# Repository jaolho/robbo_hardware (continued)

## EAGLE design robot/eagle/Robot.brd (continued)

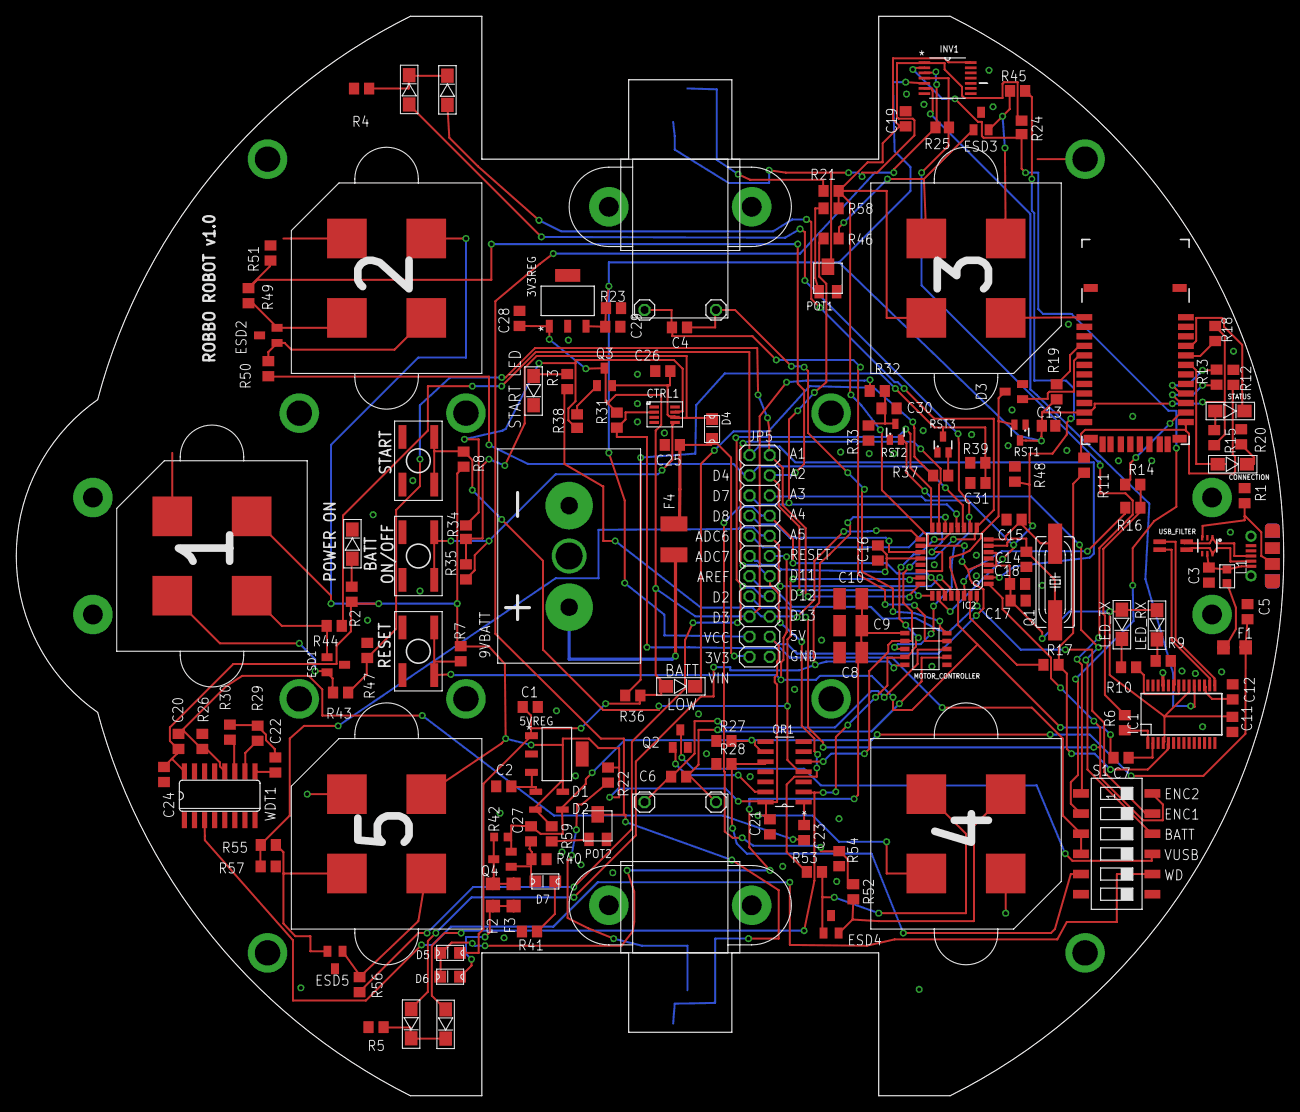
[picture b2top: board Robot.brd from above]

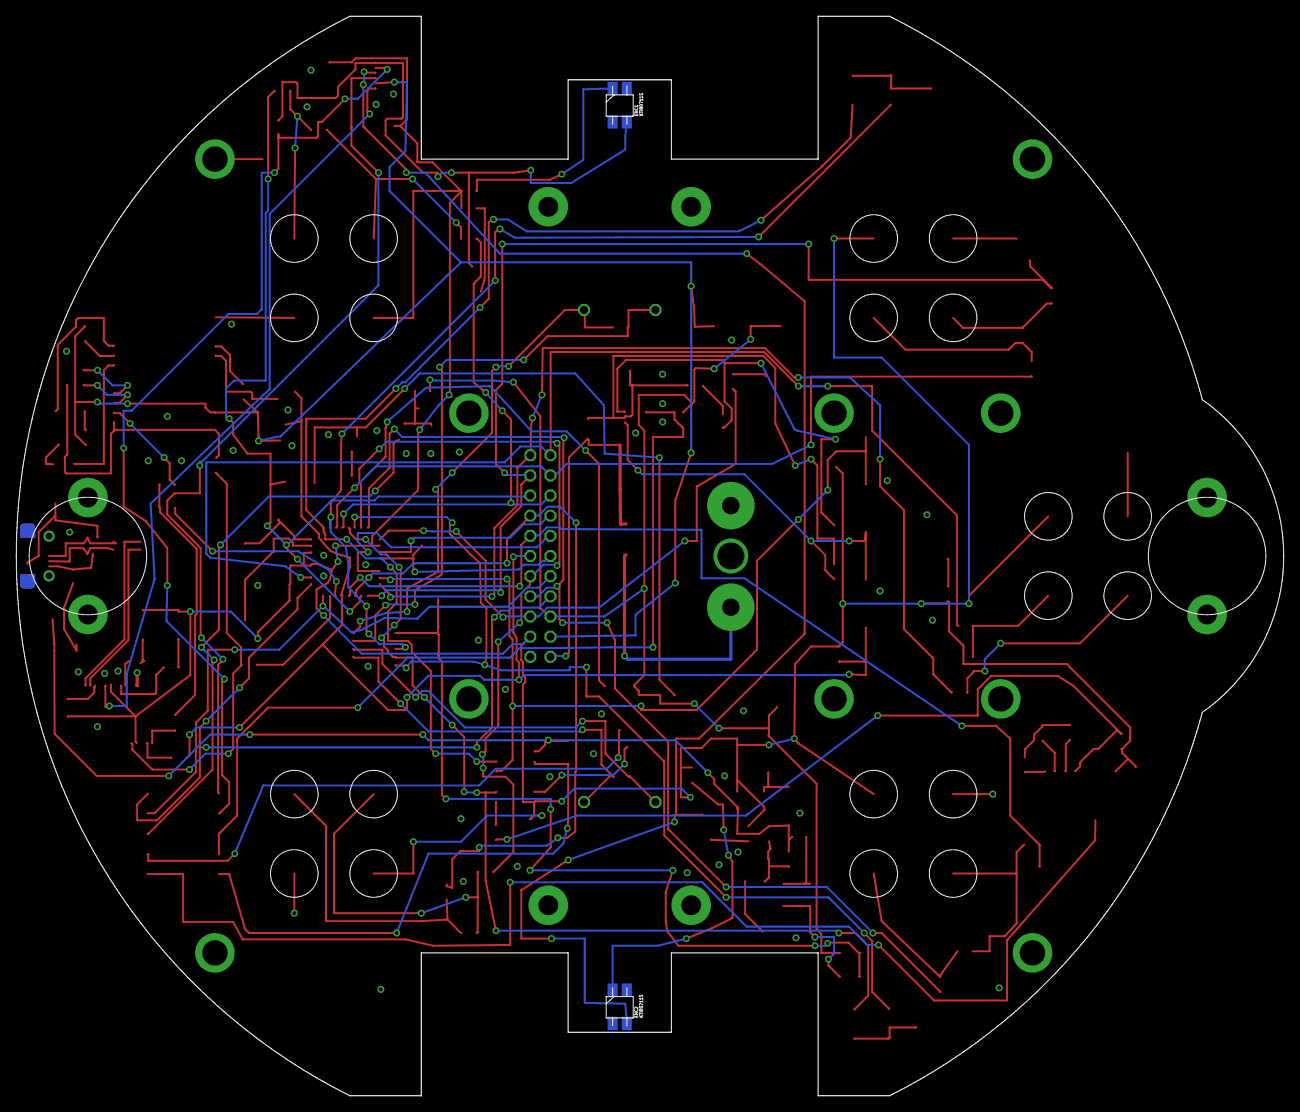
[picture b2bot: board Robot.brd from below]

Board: 2 copper layers, 159.7 x 136.0 mm, 159 parts (2 on the bottom side), 113 nets.

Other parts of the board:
U$3, U$4: MOTOR_HOLDER

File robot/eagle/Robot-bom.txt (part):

Partlist exported from D:/git/sduino/robot/eagle/Robot.sch at 25/01/2016 14:13:41

Part              Value               Device               Package                        Description                                                                                 FARNELL MF                        MOUSER_PART_NO   MPN                  OC_FARNELL OC_NEWARK PACKAGE   SUPPLIER         
3V3REG            UA78M33CDCY         UA78M33CDCY          SOT230P700X180-4N              IC, LINEAR VOLT REGULATOR, 3.3V, SOT-223-4                                                          TEXAS INSTRUMENTS                          UA78M33CDCY          2296031    03P0895   SOT-223-4 TEXAS INSTRUMENTS
5VREG             UA78M05CDCY         UA78M05CDCY          SOT230P700X180-4N              IC, LINEAR VOLT REGULATOR, 5V                                                                       TEXAS INSTRUMENTS                          UA78M05CDCY          2296030    77C1885   SOT-223-3 TEXAS INSTRUMENTS
9VBATT            BATTERY_9V          BATTERY_9V           BATTERY_PAC                                                                                                                        KEYSTONE                                   967                  1888429                                         
BT_MODULE         RN42-I/RM           BLUETOOTH-RN42"      RN42                           Bluetooth SMD module                                                                                MICROCHIP                                  RN42-I/RM            2143310                                         
BUTTON_ON_OFF     KSC921J             KSC921J              TACT_SWITCH_4_PIN              Tactile Switch                                                                                      C & K COMPONENTS                           KSC921J LFS          2435155                                         
BUTTON_PROG_START KSC921J             KSC921J              TACT_SWITCH_4_PIN              Tactile Switch                                                                                      C & K COMPONENTS                           KSC921J LFS          2435155                                         
BUTTON_RESET      KSC921J             KSC921J              TACT_SWITCH_4_PIN              Tactile Switch                                                                                      C & K COMPONENTS                           KSC921J LFS          2435155                                         
C1                330nF               C-EUC0805            C0805                          CAPACITOR, European symbol                                                                          AVX                                        08053C334KAT2A       1833878                                         
C2                100nF               C-EUC0805            C0805                          CAPACITOR, European symbol                                                                          AVX                                        08055C104KAT2A       499687                                          
C3                10nF                C-EUC0805            C0805                          CAPACITOR, European symbol                                                                          MULTICOMP                                  MC0805B103K500CT     1759246                                         
C4                100nF               C-EUC0805            C0805                          CAPACITOR, European symbol                                                                          AVX                                        08055C104KAT2A       499687                                          
C5                4.7uF               C-EUC0805            C0805                          CAPACITOR, European symbol                                                                          MURATA                                     GRM21BR61E475KA12L   1735529                                         
C6                100nF               C-EUC0805            C0805                          CAPACITOR, European symbol                                                                          AVX                                        08055C104KAT2A       499687                                          
C7                100nF               C-EUC0805            C0805                          CAPACITOR, European symbol                                                                          AVX                                        08055C104KAT2A       499687                                          
C8                47uF                C-EUC1210            C1210                          CAPACITOR, European symbol                                                                          MURATA                                     GRM32EC81C476KE15L   1907527                                         
C9                47uF                C-EUC1210            C1210                          CAPACITOR, European symbol                                                                          MURATA                                     GRM32EC81C476KE15L   1907527                                         
C10               47uF                C-EUC1210            C1210                          CAPACITOR, European symbol                                                                          MURATA                                     GRM32EC81C476KE15L   1907527                                         
C11               100nF               C-EUC0805            C0805                          CAPACITOR, European symbol                                                                          AVX                                        08055C104KAT2A       499687                                          
C12               100nF               C-EUC0805            C0805                          CAPACITOR, European symbol                                                                          AVX                                        08055C104KAT2A       499687                                          
C13               100nF               C-EUC0805            C0805                          CAPACITOR, European symbol                                                                          AVX                                        08055C104KAT2A       499687                                          
C14               22pF                C-EUC0805            C0805                          CAPACITOR, European symbol                                                                          YAGEO (PHYCOMP)                            CC0805JRNPO9BN220    1362555                                         
C15               22pF                C-EUC0805            C0805                          CAPACITOR, European symbol                                                                          YAGEO (PHYCOMP)                            CC0805JRNPO9BN220    1362555                                         
C16               100nF               C-EUC0805            C0805                          CAPACITOR, European symbol                                                                          AVX                                        08055C104KAT2A       499687                                          
C17               4.7uF               C-EUC0805            C0805                          CAPACITOR, European symbol                                                                          MURATA                                     GRM21BR61E475KA12L   1735529                                         
C18               100nF               C-EUC0805            C0805                          CAPACITOR, European symbol                                                                          AVX                                        08055C104KAT2A       499687                                          
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
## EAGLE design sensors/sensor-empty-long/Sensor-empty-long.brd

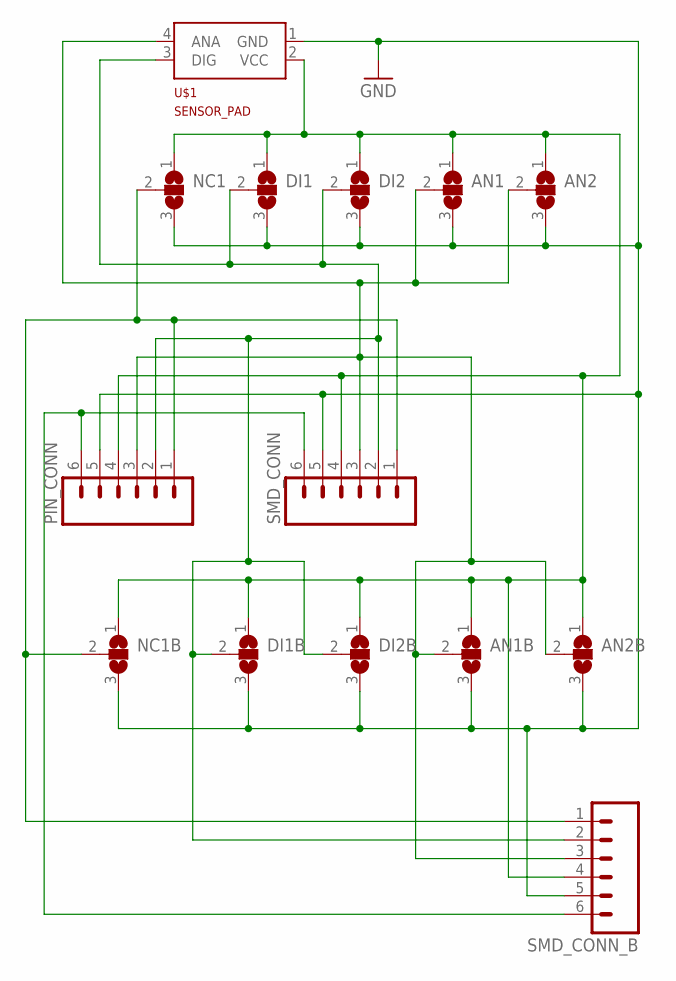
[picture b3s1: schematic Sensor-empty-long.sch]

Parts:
AN1, AN1B, AN2, AN2B: SJ2W; SJ_2
DI1, DI1B, DI2, DI2B: SJ2W; SJ_2
NC1, NC1B: SJ2W; SJ_2
PIN_CONN: M06SILK_FEMALE_PTH; 1X06
SMD_CONN: M06SMD-STRAIGHT-COMBO-FEMALE; 1X06_SMD_STRAIGHT_COMBO; MPN BG306-06-A-1-0400-L-B
SMD_CONN_B: M06SMD-STRAIGHT-COMBO-FEMALE; 1X06_SMD_STRAIGHT_COMBO; MPN BG306-06-A-1-0400-L-B
U$1: SENSOR_PAD

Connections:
GND: AN1.3, AN1B.3, AN2.3, AN2B.3, DI1.3, DI1B.3, DI2.3, DI2B.3, NC1.3, NC1B.3, PIN_CONN.5, SMD_CONN.5, SMD_CONN_B.5, U$1.1 (GND)
unnamed: AN1.2, AN1B.2, AN2.2, AN2B.2, PIN_CONN.3, SMD_CONN.3, SMD_CONN_B.3, U$1.4 (ANA)
unnamed: NC1.2, NC1B.2, PIN_CONN.1, SMD_CONN.1, SMD_CONN_B.1
unnamed: AN1.1, AN1B.1, AN2.1, AN2B.1, DI1.1, DI1B.1, DI2.1, DI2B.1, NC1.1, NC1B.1, PIN_CONN.4, SMD_CONN.4, SMD_CONN_B.4, U$1.2 (VCC)
unnamed: PIN_CONN.6, SMD_CONN.6, SMD_CONN_B.6
unnamed: DI1.2, DI1B.2, DI2.2, DI2B.2, PIN_CONN.2, SMD_CONN.2, SMD_CONN_B.2, U$1.3 (DIG)

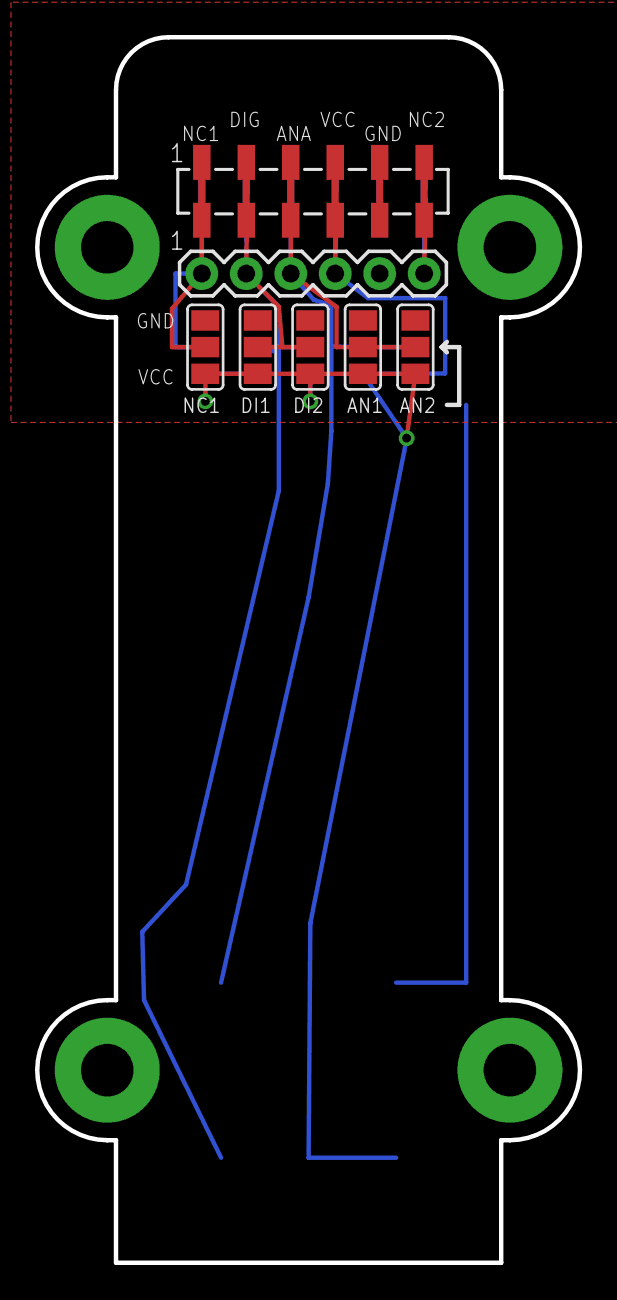
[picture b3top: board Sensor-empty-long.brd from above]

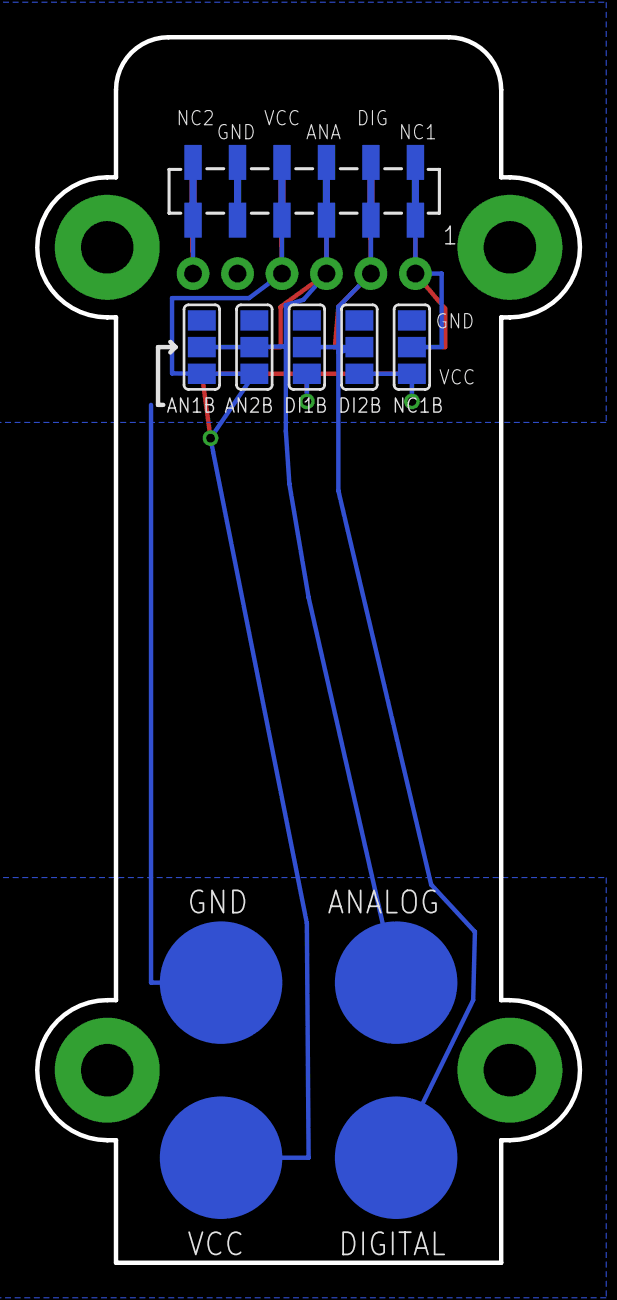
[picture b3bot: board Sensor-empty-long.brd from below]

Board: 2 copper layers, 31.0 x 70.0 mm, 14 parts (6 on the bottom side), 6 nets.

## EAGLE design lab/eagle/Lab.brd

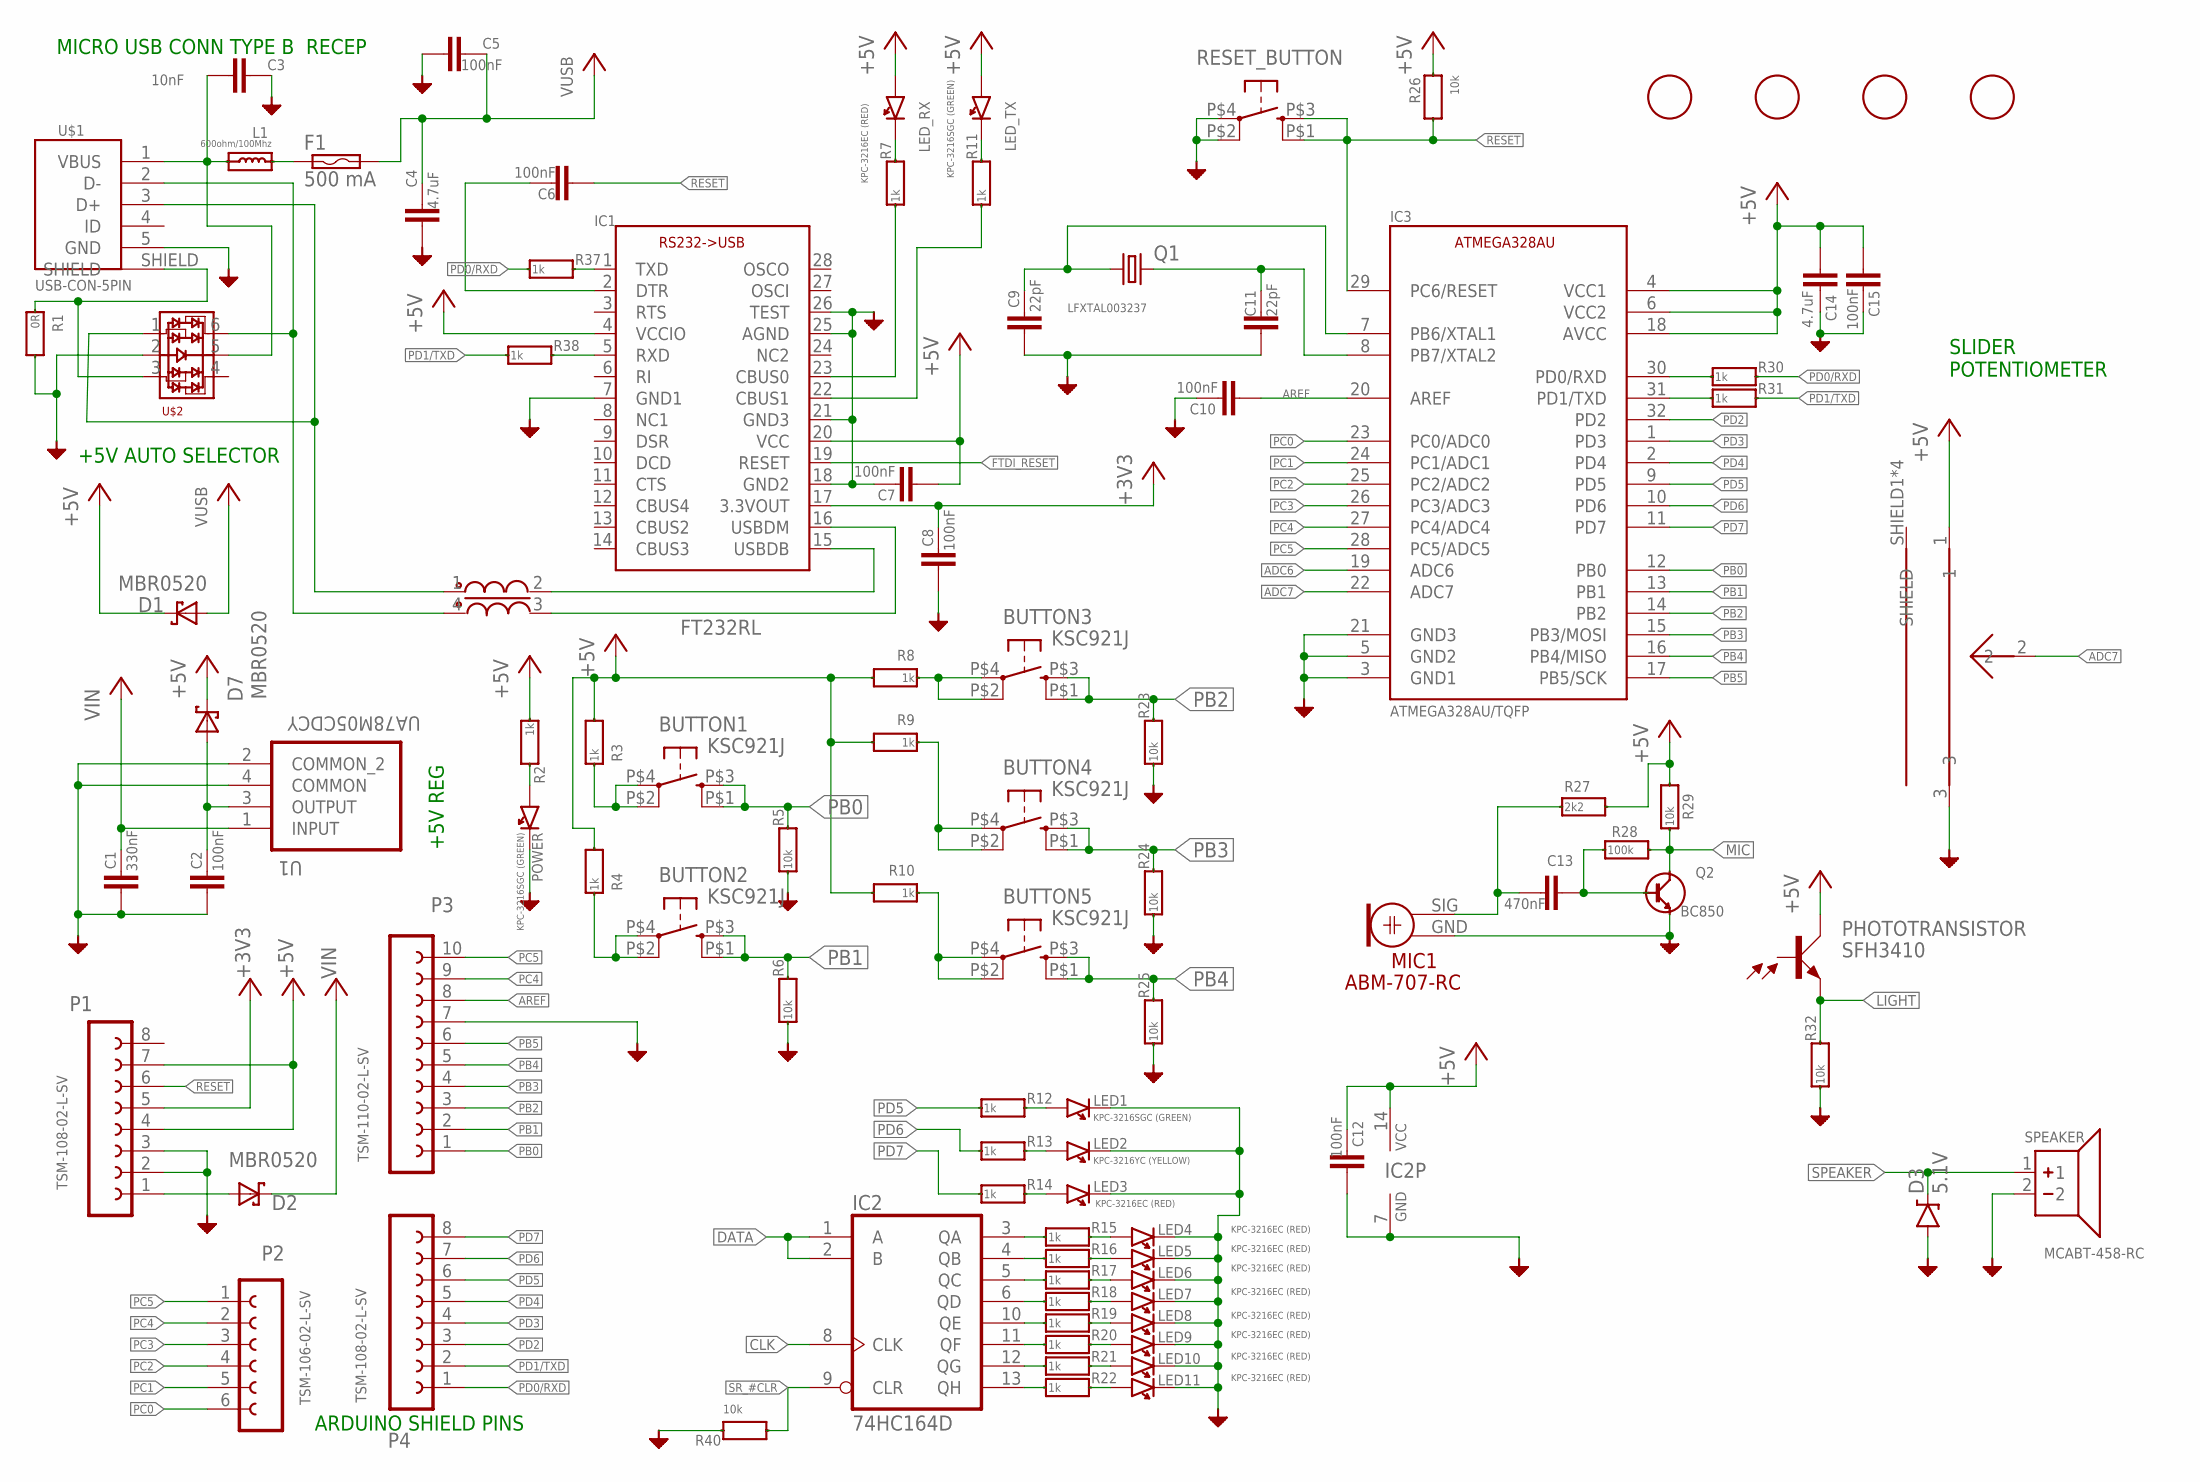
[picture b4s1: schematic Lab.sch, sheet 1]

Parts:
BUTTON1, BUTTON2, BUTTON3, BUTTON4, BUTTON5: KSC921J; TACT_SWITCH_4_PIN; MPN KSC921J LFS
C1: 330nF; C0805; MPN 08053C334KAT2A
C2, C5, C6, C7, C8, C10, C12, C15: 100nF; C0805; MPN 08055C104KAT2A
C3: 10nF; C0805; MPN MC0805B103K500CT
C4, C14: 4.7uF; C0805; MPN 0805X475K250CT
C9, C11: 22pF; C0805; MPN CC0805JRNPO9BN220
C13: 470nF; C0805; MPN MC0805F474Z250CT
D1, D2, D7: MBR0520; SOD123; MPN MBR0520L
D3: 5.1V; SOD-323; MPN MM3Z5V1T1G
F1: 500 mA; PT1206; MPN NANOSMDC050F/13.2-2
IC1: FT232RL; SSOP28; MPN FT232RL-REEL
IC2: 74HC164D; SO14; MPN 74HC164D
IC3: ATMEGA328AU/TQFP; TQFP32-08; MPN ATMEGA328P-AU
L1: 600ohm/100Mhz; R0603; MPN 742792651
LED1: KPC-3216SGC (GREEN); LED3216_PAC; MPN KPC-3216SGC
LED2: KPC-3216YC (YELLOW); LED3216_PAC; MPN KPC-3216YC
LED3, LED4, LED5, LED6, LED7, LED8, LED9, LED10, LED11: KPC-3216EC (RED); LED3216_PAC; MPN KPC-3216EC
LED_RX: KPC-3216EC (RED); LED3216_PAC; MPN KPC-3216EC
LED_TX: KPC-3216SGC (GREEN); LED3216_PAC; MPN KPC-3216SGC
MIC1: ABM-707-RC; MPN ABM-707-RC
P1, P4: TSM-108-02-L-SV; FE08; MPN 2212S-08SG-85
P2: TSM-106-02-L-SV; FE06; MPN 2212S-06SG-85
P3: TSM-110-02-L-SV; FE10; MPN 2212S-10SG-85
PHOTOTRANSISTOR: SFH3410SMD; SFH3410; MPN SFH3410-Z
POWER: KPC-3216SGC (GREEN); LED3216_PAC; MPN KPC-3216SGC
Q1: LFXTAL003237; SM49; MPN LFXTAL003237
Q2: BC850; MY_SOT23; MPN BC850C,215
R1: 0R; R0805; MPN MC01W08050R
R2, R3, R4, R7, R8, R9, R10, R11, R12, R13, R14, R15, R16, R17, R18, R19, R20, R21, R22, R30, R31, R37, R38: 1k; R0805; MPN CRCW08051K00FKTA
R5, R6, R23, R24, R25, R26, R29, R32, R40: 10k; R0805; MPN RC0805FR-0710KL
R27: 2k2; R0805; MPN RC0805FR-072K2L.
R28: 100k; R0805; MPN RC0805FR-07100KL
RESET_BUTTON: KSC921J; TACT_SWITCH_4_PIN; MPN KSC921J LFS
SLIDER_RESISTOR: PTA4543; MPN PTA4543-2015DPB103
SPEAKER: MCABT-458-RC; SMD_SPK_PAC; MPN MCABT-458-RC
U1: UA78M05CDCY; SOT230P700X180-4N
U$1: USB-CON-5PIN; USB-MICRO-MOLEX-105017-0001_V2; MPN 105017-0001
U$2: PRTR5V0U4Y; SOT363; MPN PRTR5V0U4Y,125
U$3, U$4, U$5, U$6: FIDUCIAL; FIDUCIAL_1MM
USB_FILTER: SRF3216A; MPN SRF3216A-900Y

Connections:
+3V3: C8.1, IC1.17 (3.3VOUT), P1.5
+5V: C7.2, C12.2, C14.2, C15.2, D1.1 (K), D7.1 (K), IC1.4 (VCCIO), IC1.20 (VCC), IC2.14 (VCC), IC3.4 (VCC1), IC3.6 (VCC2), IC3.18 (AVCC), LED_RX.1, LED_TX.1, P1.4, P1.7, PHOTOTRANSISTOR.COLLECTOR, R2.1, R3.2, R4.2, R8.2, R9.2, R10.2, R26.2, R27.2, R29.2, SLIDER_RESISTOR.1; also elsewhere on the board
ADC6: IC3.19 (ADC6)
ADC7: IC3.22 (ADC7), SLIDER_RESISTOR.2
AREF: C10.2, IC3.20 (AREF), P3.8
CLK: IC2.8 (CLK); also elsewhere on the board
DATA: IC2.1 (A), IC2.2 (B); also elsewhere on the board
FTDI_RESET: IC1.19 (RESET); also elsewhere on the board
GND: C1.2, C2.2, C3.1, C4.2, C5.2, C7.1, C8.2, C9.2, C10.1, C11.2, C12.1, C14.1, C15.1, D3.A, IC1.7 (GND1), IC1.18 (GND2), IC1.21 (GND3), IC1.25 (AGND), IC1.26 (TEST), IC2.7 (GND), IC3.3 (GND1), IC3.5 (GND2), IC3.21 (GND3), LED1.2, LED2.2, LED3.2, LED4.2, LED5.2, LED6.2, LED7.2, LED8.2, LED9.2, LED10.2, LED11.2, MIC1.GND (2), P1.2, P1.3, P3.7, POWER.2, Q2.2, R1.2, R5.1, R6.1, R23.1, R24.1, R25.1, R32.1, R40.2, RESET_BUTTON.P$2 (2), RESET_BUTTON.P$4 (1), SLIDER_RESISTOR.3, SPEAKER.2, U1.2 (COMMON_2), U1.4 (COMMON), U$1.5 (GND), U$2.2; also elsewhere on the board
LIGHT: PHOTOTRANSISTOR.EMITTER, R32.2; also elsewhere on the board
MIC: Q2.3, R28.2, R29.1; also elsewhere on the board
unnamed: C11.1, IC3.8 (PB7/XTAL2), Q1.2
unnamed: C9.1, IC3.7 (PB6/XTAL1), Q1.1
unnamed: LED5.1, R16.2
unnamed: LED3.1, R14.2
unnamed: LED2.1, R13.2
unnamed: LED1.1, R12.2
unnamed: LED4.1, R15.2
unnamed: LED6.1, R17.2
unnamed: LED7.1, R18.2
unnamed: LED8.1, R19.2
unnamed: LED9.1, R20.2
unnamed: D2.2 (A), P1.1
unnamed: LED10.1, R21.2
unnamed: IC1.23 (CBUS0), R7.1
unnamed: C6.1, IC1.2 (DTR)
unnamed: POWER.1, R2.2
unnamed: IC1.15 (USBDB), USB_FILTER.2
unnamed: IC1.16 (USBDM), USB_FILTER.3
unnamed: LED11.1, R22.2
unnamed: IC3.30 (PD0/RXD), R30.1
unnamed: IC2.3 (QA), R15.1
unnamed: IC2.4 (QB), R16.1
unnamed: IC2.5 (QC), R17.1
unnamed: LED_RX.2, R7.2
unnamed: LED_TX.2, R11.2
unnamed: IC1.22 (CBUS1), R11.1
unnamed: U$1.3 (D+), U$2.1, USB_FILTER.1
unnamed: IC3.31 (PD1/TXD), R31.1
unnamed: BUTTON1.P$2 (2), BUTTON1.P$4 (1), R3.1
unnamed: BUTTON2.P$2 (2), BUTTON2.P$4 (1), R4.1
unnamed: U$1.2 (D-), U$2.6, USB_FILTER.4
unnamed: BUTTON4.P$2 (2), BUTTON4.P$4 (1), R9.1
unnamed: BUTTON5.P$2 (2), BUTTON5.P$4 (1), R10.1
unnamed: BUTTON3.P$2 (2), BUTTON3.P$4 (1), R8.1
unnamed: F1.1A (1), F1.1B (1), L1.1
unnamed: IC1.5 (RXD), R38.2
unnamed: IC1.1 (TXD), R37.2
unnamed: C2.1, D7.2 (A), U1.3 (OUTPUT)
unnamed: IC2.6 (QD), R18.1
unnamed: IC2.10 (QE), R19.1
unnamed: IC2.11 (QF), R20.1
unnamed: IC2.12 (QG), R21.1
unnamed: IC2.13 (QH), R22.1
unnamed: C13.1, Q2.1, R28.1
unnamed: C13.2, MIC1.SIG (1), R27.1
unnamed: C3.2, L1.2, U$1.1 (VBUS), U$2.5
PB0: BUTTON1.P$1 (4), BUTTON1.P$3 (3), IC3.12 (PB0), P3.1, R5.2
PB1: BUTTON2.P$1 (4), BUTTON2.P$3 (3), IC3.13 (PB1), P3.2, R6.2
PB2: BUTTON3.P$1 (4), BUTTON3.P$3 (3), IC3.14 (PB2), P3.3, R23.2
PB3: BUTTON4.P$1 (4), BUTTON4.P$3 (3), IC3.15 (PB3/MOSI), P3.4, R24.2
PB4: BUTTON5.P$1 (4), BUTTON5.P$3 (3), IC3.16 (PB4/MISO), P3.5, R25.2
PB5: IC3.17 (PB5/SCK), P3.6; also elsewhere on the board
PC0: IC3.23 (PC0/ADC0), P2.6; also elsewhere on the board
PC1: IC3.24 (PC1/ADC1), P2.5; also elsewhere on the board
PC2: IC3.25 (PC2/ADC2), P2.4
PC3: IC3.26 (PC3/ADC3), P2.3; also elsewhere on the board
PC4: IC3.27 (PC4/ADC4), P2.2, P3.9; also elsewhere on the board
PC5: IC3.28 (PC5/ADC5), P2.1, P3.10; also elsewhere on the board
PD0/RXD: P4.1, R30.2, R37.1
PD1/TXD: P4.2, R31.2, R38.1
PD2: IC3.32 (PD2), P4.3; also elsewhere on the board
PD3: IC3.1 (PD3), P4.4; also elsewhere on the board
PD4: IC3.2 (PD4), P4.5; also elsewhere on the board
PD5: IC3.9 (PD5), P4.6, R12.1
PD6: IC3.10 (PD6), P4.7, R13.1
PD7: IC3.11 (PD7), P4.8, R14.1
RESET: C6.2, IC3.29 (PC6/RESET), P1.6, R26.1, RESET_BUTTON.P$1 (4), RESET_BUTTON.P$3 (3)
SHIELD1: R1.1, U$1.SHIELD, U$2.3
SPEAKER: D3.C, SPEAKER.1; also elsewhere on the board
SR_#CLR: IC2.9 (CLR), R40.1; also elsewhere on the board
USB_VCC: C4.1, C5.1, D1.2 (A), F1.2A (2), F1.2B (2)
VIN: C1.1, D2.1 (K), U1.1 (INPUT)

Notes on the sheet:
SLIDER POTENTIOMETER
+5V AUTO SELECTOR
+5V REG
ARDUINO SHIELD PINS
MICRO USB CONN TYPE B RECEP

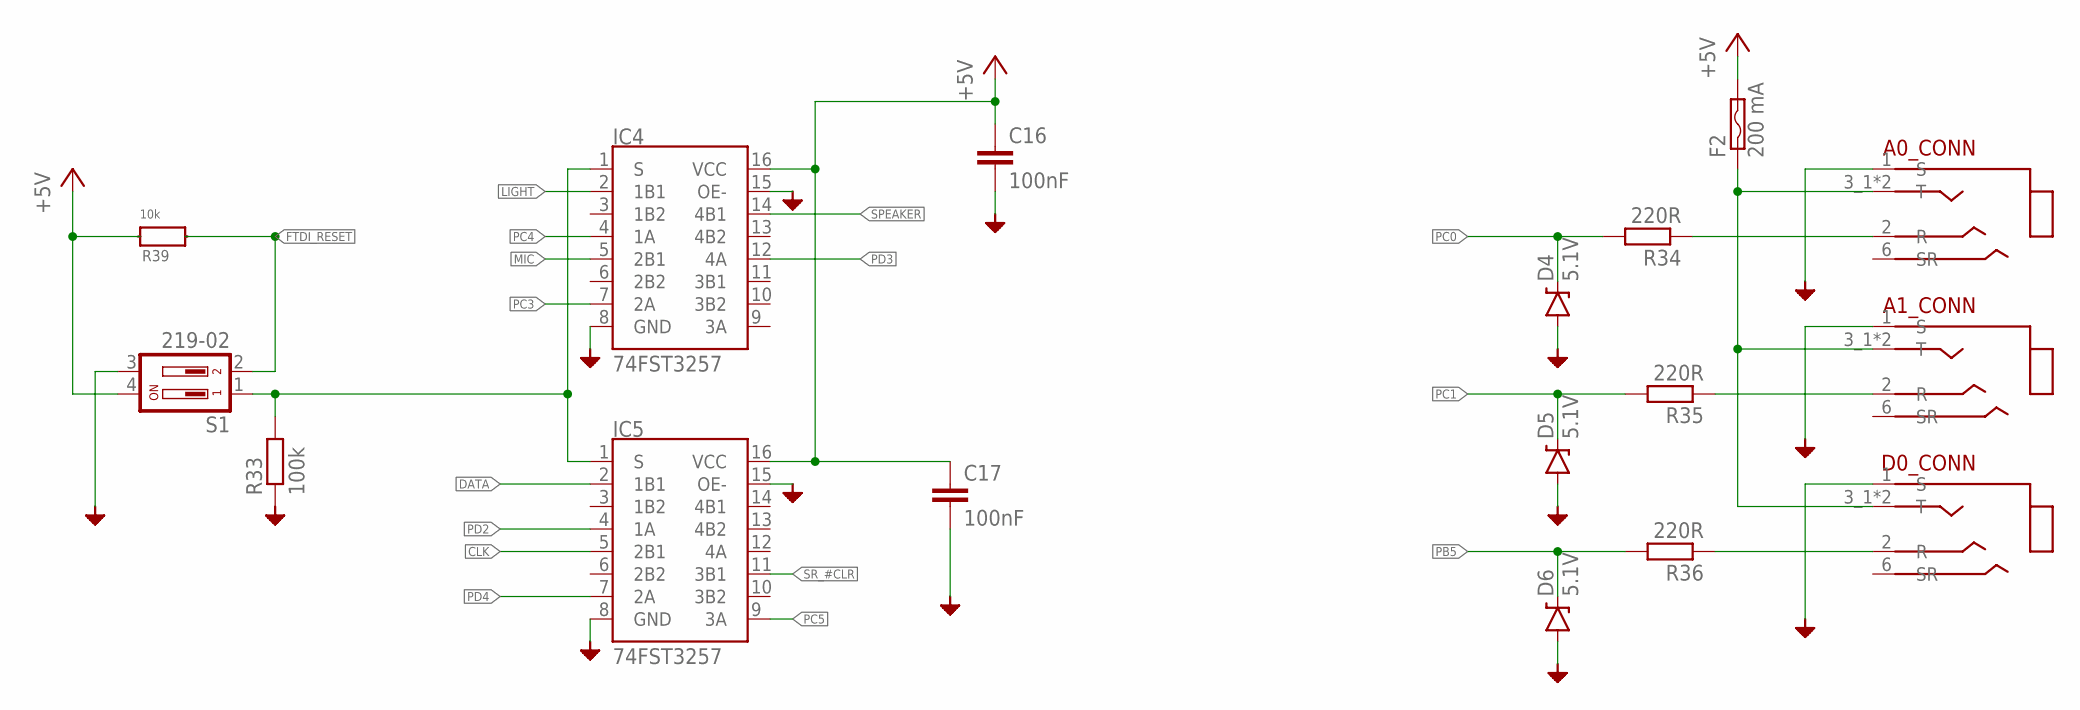
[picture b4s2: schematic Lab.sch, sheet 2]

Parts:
A0_CONN, A1_CONN: FC68125; MPN FC68125
C16, C17: 100nF; C0805; MPN 08055C104KAT2A
D0_CONN: FC68125; MPN FC68125
D4, D5, D6: 5.1V; SOD-323; MPN MM3Z5V1T1G
F2: 200 mA; PT1206; MPN NANOSMDC020F-2
IC4, IC5: 74FST3257; SO16; MPN 74FST3257DR2G
R33: 100k; R0805; MPN RC0805FR-07100KL
R34, R35, R36: 220R; M0805; MPN MCWR08X2200FTL
R39: 10k; R0805; MPN RC0805FR-0710KL
S1: 219-02; CTS-219-02; MPN MCEMR-02-T

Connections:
+5V: C16.1, C17.1, F2.2A (2), F2.2B (2), IC4.16 (VCC), IC5.16 (VCC), R39.2, S1.4; also elsewhere on the board
+5V_FUSED: A0_CONN.3_1 (T), A0_CONN.3_2 (T), A1_CONN.3_1 (T), A1_CONN.3_2 (T), D0_CONN.3_1 (T), D0_CONN.3_2 (T), F2.1A (1), F2.1B (1)
CLK: IC5.5 (2B1); also elsewhere on the board
DATA: IC5.2 (1B1); also elsewhere on the board
FTDI_RESET: R39.1, S1.2; also elsewhere on the board
GND: A0_CONN.1 (S), A1_CONN.1 (S), C16.2, C17.2, D0_CONN.1 (S), D4.A, D5.A, D6.A, IC4.8 (GND), IC4.15 (OE-), IC5.8 (GND), IC5.15 (OE-), R33.1, S1.3; also elsewhere on the board
LIGHT: IC4.2 (1B1); also elsewhere on the board
MIC: IC4.5 (2B1); also elsewhere on the board
unnamed: IC4.1 (S), IC5.1 (S), R33.2, S1.1
unnamed: A1_CONN.2 (R), R35.1
unnamed: A0_CONN.2 (R), R34.1
unnamed: D0_CONN.2 (R), R36.1
PB5: D6.C, R36.2; also elsewhere on the board
PC0: D4.C, R34.2; also elsewhere on the board
PC1: D5.C, R35.2; also elsewhere on the board
PC3: IC4.7 (2A); also elsewhere on the board
PC4: IC4.4 (1A); also elsewhere on the board
PC5: IC5.9 (3A); also elsewhere on the board
PD2: IC5.4 (1A); also elsewhere on the board
PD3: IC4.12 (4A); also elsewhere on the board
PD4: IC5.7 (2A); also elsewhere on the board
SPEAKER: IC4.14 (4B1); also elsewhere on the board
SR_#CLR: IC5.11 (3B1); also elsewhere on the board
